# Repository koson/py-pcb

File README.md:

# py-pcb
pcb dei sistemi py-acqua e py-home

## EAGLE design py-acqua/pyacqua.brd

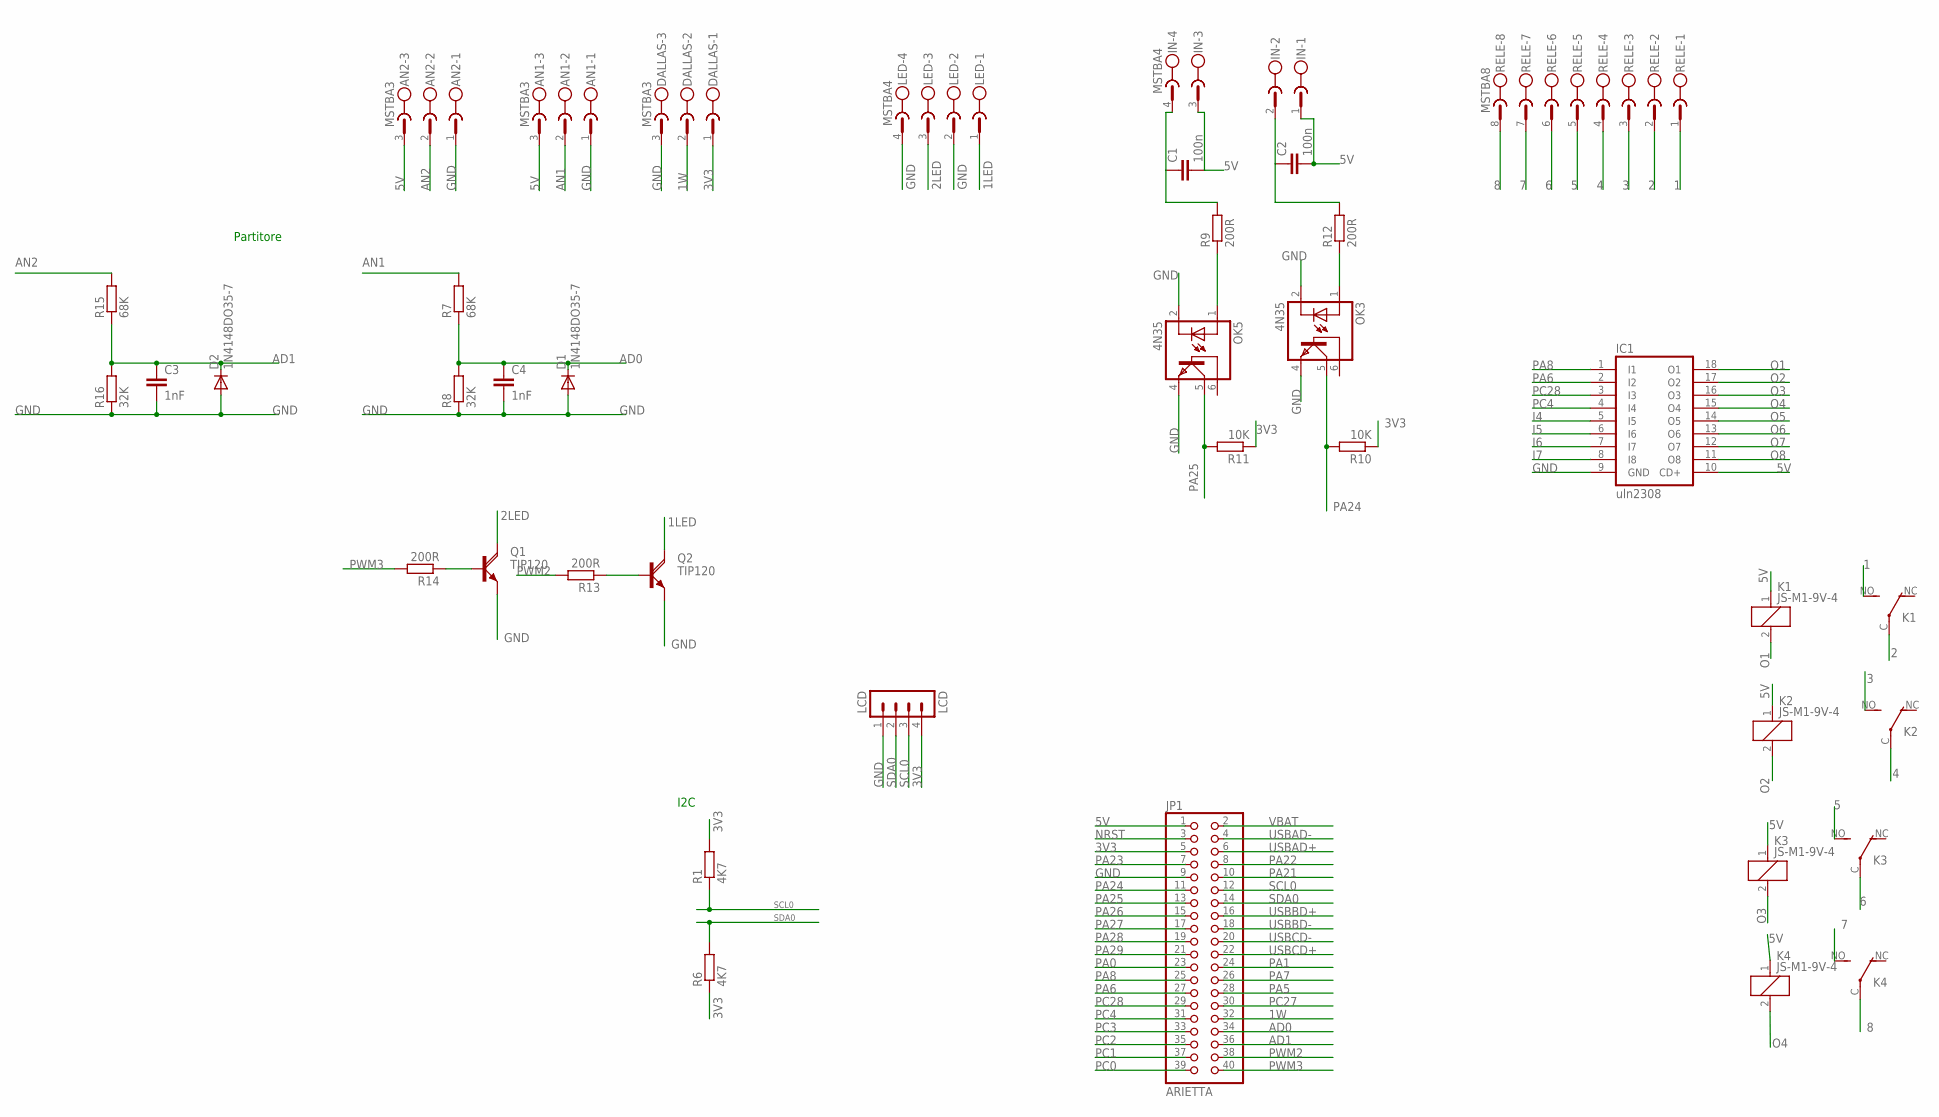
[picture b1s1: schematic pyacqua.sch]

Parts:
AN1, AN2: MSTBA3
C1, C2: 100n; C2.5-3
C3, C4: 1nF; C2.5-3
D1, D2: 1N4148DO35-7; DO35-7
DALLAS: MSTBA3
IC1: uln2308; DIL18
IN: MSTBA4
JP1: ARIETTA; 2X20
K1, K2, K3, K4: JS-M1-9V-4; JS-M
LCD: LCD; MA04-1
LED: MSTBA4
OK3, OK5: 4N35; DIL06
Q1, Q2: TIP120; TO220AH
R1, R6: 4K7; 0204V
R7, R15: 68K; 0204V
R8, R16: 32K; 0204V
R9, R12, R13, R14: 200R; 0204V
R10, R11: 10K; 0204V
RELE: MSTBA8

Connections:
1: K1.NO (S), RELE.1
1LED: LED.1, Q2.C
1W: DALLAS.2, JP1.32
2: K1.C, RELE.2
2LED: LED.3, Q1.C
3: K2.NO (S), RELE.3
3V3: DALLAS.1, JP1.5, LCD.4, R1.2, R6.1, R10.1, R11.1
4: K2.C, RELE.4
5: K3.NO (S), RELE.5
5V: AN1.3, AN2.3, C1.2, C2.2, IC1.10 (CD+), IN.1, IN.3, JP1.1, K1.1, K2.1, K3.1, K4.1
6: K3.C, RELE.6
7: K4.NO (S), RELE.7
8: K4.C, RELE.8
AD0: C4.1, D1.C, JP1.34, R7.1, R8.2
AD1: C3.1, D2.C, JP1.36, R15.1, R16.2
AN1: AN1.2, R7.2
AN2: AN2.2, R15.2
GND: AN1.1, AN2.1, C3.2, C4.2, D1.A, D2.A, DALLAS.3, IC1.9 (GND), JP1.9, LCD.1, LED.2, LED.4, OK3.2 (C), OK3.4 (EMI), OK5.2 (C), OK5.4 (EMI), Q1.E, Q2.E, R8.1, R16.1
I4: IC1.5 (I5)
I5: IC1.6 (I6)
I6: IC1.7 (I7)
I7: IC1.8 (I8)
unnamed: OK5.1 (A), R9.1
unnamed: OK3.1 (A), R12.1
unnamed: C2.1, IN.2, R12.2
unnamed: Q2.B, R13.1
unnamed: C1.1, IN.4, R9.2
unnamed: Q1.B, R14.1
NRST: JP1.3
O1: IC1.18 (O1), K1.2
O2: IC1.17 (O2), K2.2
O3: IC1.16 (O3), K3.2
O4: IC1.15 (O4), K4.2
O5: IC1.14 (O5)
O6: IC1.13 (O6)
O7: IC1.12 (O7)
O8: IC1.11 (O8)
PA0: JP1.23
PA1: JP1.24
PA5: JP1.28
PA6: IC1.2 (I2), JP1.27
PA7: JP1.26
PA8: IC1.1 (I1), JP1.25
PA21: JP1.10
PA22: JP1.8
PA23: JP1.7
PA24: JP1.11, OK3.5 (COL), R10.2
PA25: JP1.13, OK5.5 (COL), R11.2
PA26: JP1.15
PA27: JP1.17
PA28: JP1.19
PA29: JP1.21
PC0: JP1.39
PC1: JP1.37
PC2: JP1.35
PC3: JP1.33
PC4: IC1.4 (I4), JP1.31
PC27: JP1.30
PC28: IC1.3 (I3), JP1.29
PWM2: JP1.38, R13.2
PWM3: JP1.40, R14.2
SCL0: JP1.12, LCD.3, R1.1
SDA0: JP1.14, LCD.2, R6.2
USBAD+: JP1.6
USBAD-: JP1.4
USBBD+: JP1.16
USBBD-: JP1.18
USBCD+: JP1.22
USBCD-: JP1.20
VBAT: JP1.2

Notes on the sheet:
Partitore
I2C

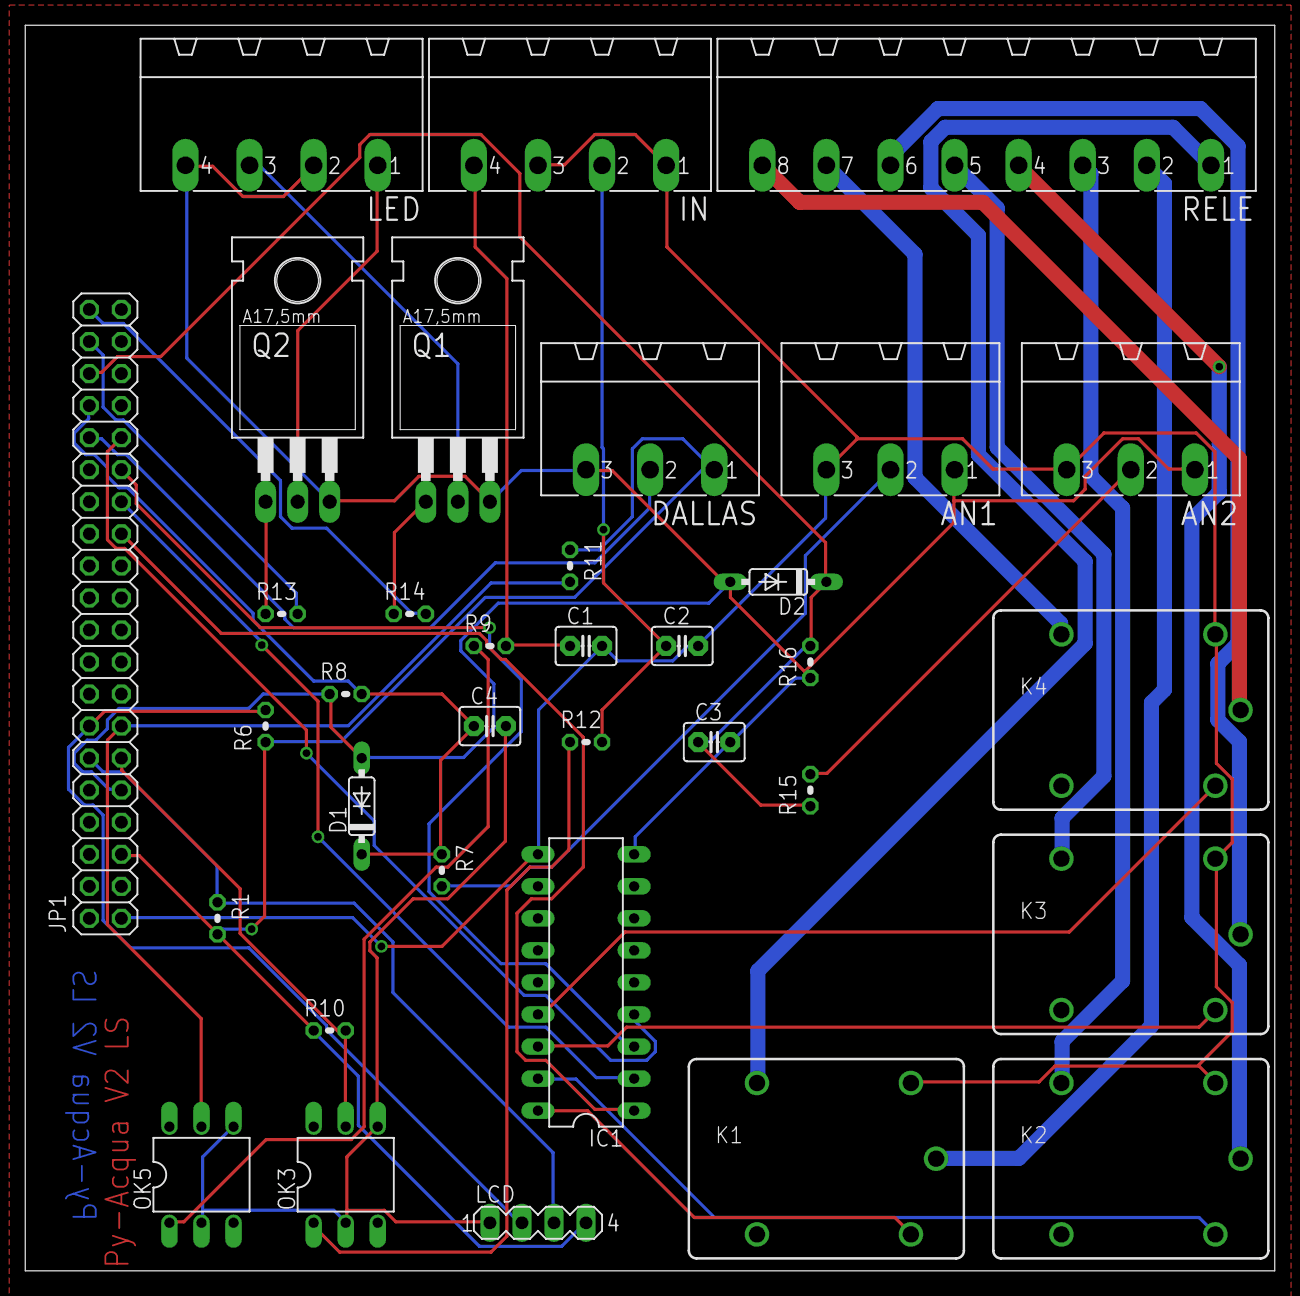
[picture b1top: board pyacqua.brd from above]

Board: 2 copper layers, 99.0 x 98.7 mm, 35 parts (0 on the bottom side), 38 nets.

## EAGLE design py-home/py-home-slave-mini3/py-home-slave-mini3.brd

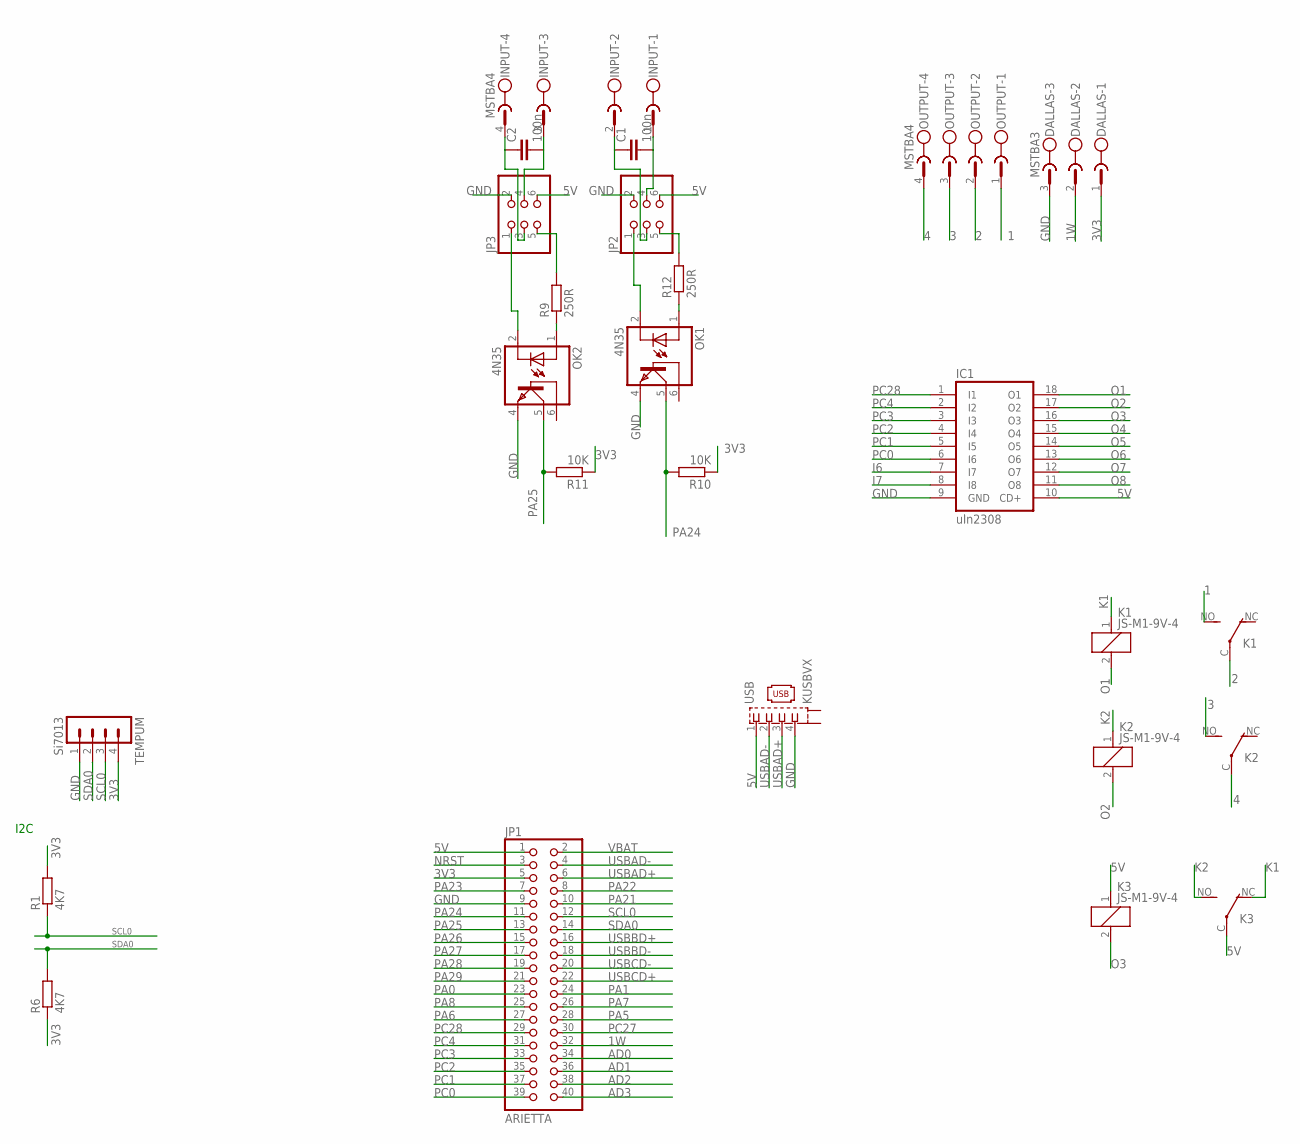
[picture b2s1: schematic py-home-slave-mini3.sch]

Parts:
C1, C2: 100n; C2.5-3
DALLAS: MSTBA3
IC1: uln2308; DIL18
INPUT: MSTBA4
JP1: ARIETTA; 2X20
JP2, JP3: PINHD-2X3; 2X03
K1, K2, K3: JS-M1-9V-4; JS-M
OK1, OK2: 4N35; DIL06
OUTPUT: MSTBA4
R1, R6: 4K7; 0204V
R9, R12: 250R; 0204V
R10, R11: 10K; 0204V
TEMPUM: Si7013; MA04-1
USB: KUSBVX

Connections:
1: K1.NO (S), OUTPUT.1
1W: DALLAS.2, JP1.32
2: K1.C, OUTPUT.2
3: K2.NO (S), OUTPUT.3
3V3: DALLAS.1, JP1.5, R1.2, R6.1, R10.1, R11.1, TEMPUM.4
4: K2.C, OUTPUT.4
5V: IC1.10 (CD+), JP1.1, JP2.6, JP3.6, K3.1, K3.C, USB.1
AD0: JP1.34
AD1: JP1.36
AD2: JP1.38
AD3: JP1.40
GND: DALLAS.3, IC1.9 (GND), JP1.9, JP2.2, JP3.2, OK1.4 (EMI), OK2.4 (EMI), TEMPUM.1, USB.4
I6: IC1.7 (I7)
I7: IC1.8 (I8)
K1: K1.1, K3.NC (O)
K2: K2.1, K3.NO (S)
unnamed: OK2.1 (A), R9.1
unnamed: C1.2, INPUT.1, JP2.4
unnamed: OK1.1 (A), R12.1
unnamed: JP2.1, OK1.2 (C)
unnamed: JP3.5, R9.2
unnamed: JP3.1, OK2.2 (C)
unnamed: JP2.5, R12.2
unnamed: C2.2, INPUT.3, JP3.4
unnamed: C1.1, INPUT.2, JP2.3
unnamed: C2.1, INPUT.4, JP3.3
NRST: JP1.3
O1: IC1.18 (O1), K1.2
O2: IC1.17 (O2), K2.2
O3: IC1.16 (O3), K3.2
O4: IC1.15 (O4)
O5: IC1.14 (O5)
O6: IC1.13 (O6)
O7: IC1.12 (O7)
O8: IC1.11 (O8)
PA0: JP1.23
PA1: JP1.24
PA5: JP1.28
PA6: JP1.27
PA7: JP1.26
PA8: JP1.25
PA21: JP1.10
PA22: JP1.8
PA23: JP1.7
PA24: JP1.11, OK1.5 (COL), R10.2
PA25: JP1.13, OK2.5 (COL), R11.2
PA26: JP1.15
PA27: JP1.17
PA28: JP1.19
PA29: JP1.21
PC0: IC1.6 (I6), JP1.39
PC1: IC1.5 (I5), JP1.37
PC2: IC1.4 (I4), JP1.35
PC3: IC1.3 (I3), JP1.33
PC4: IC1.2 (I2), JP1.31
PC27: JP1.30
PC28: IC1.1 (I1), JP1.29
SCL0: JP1.12, R1.1, TEMPUM.3
SDA0: JP1.14, R6.2, TEMPUM.2
USBAD+: JP1.6, USB.3
USBAD-: JP1.4, USB.2
USBBD+: JP1.16
USBBD-: JP1.18
USBCD+: JP1.22
USBCD-: JP1.20
VBAT: JP1.2

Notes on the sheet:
I2C

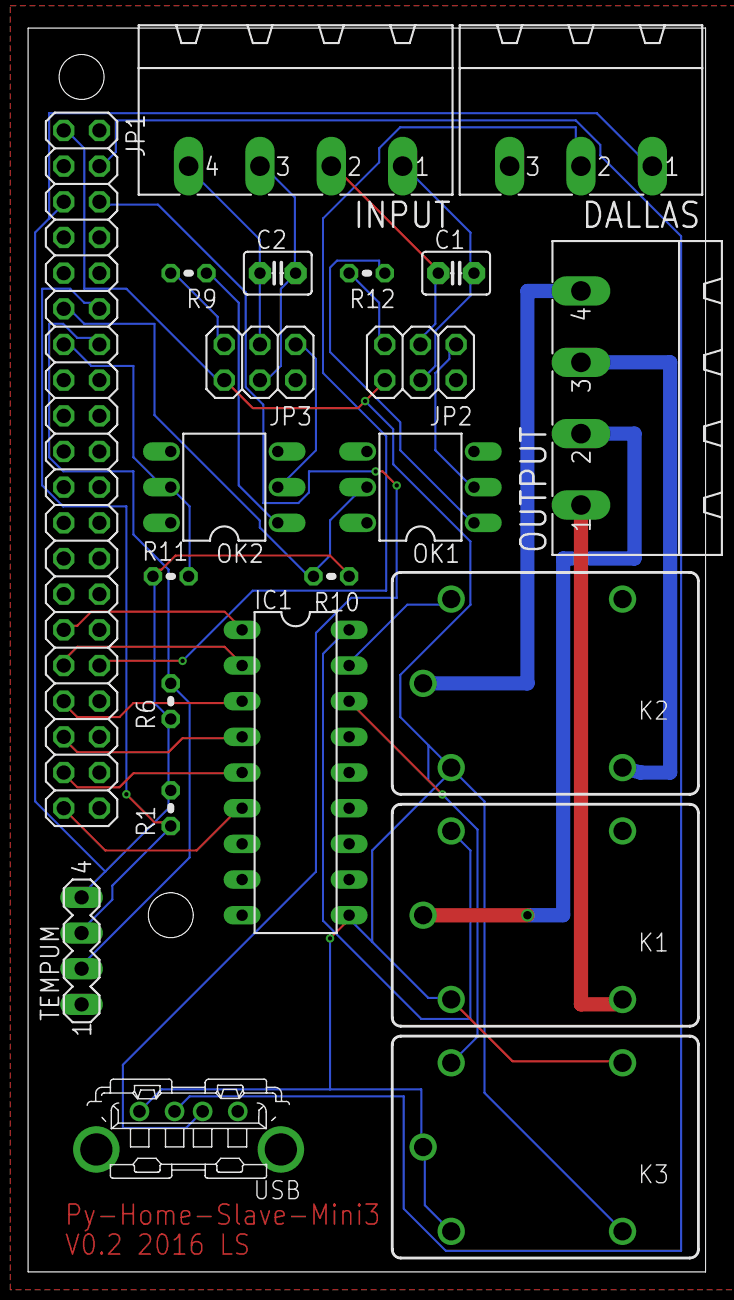
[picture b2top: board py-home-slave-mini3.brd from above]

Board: 2 copper layers, 48.2 x 88.6 mm, 22 parts (0 on the bottom side), 35 nets.

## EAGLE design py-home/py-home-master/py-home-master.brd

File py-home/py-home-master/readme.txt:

I2C
PA30 (SDA0) and PA31 (SCL0) towards 3.3V.

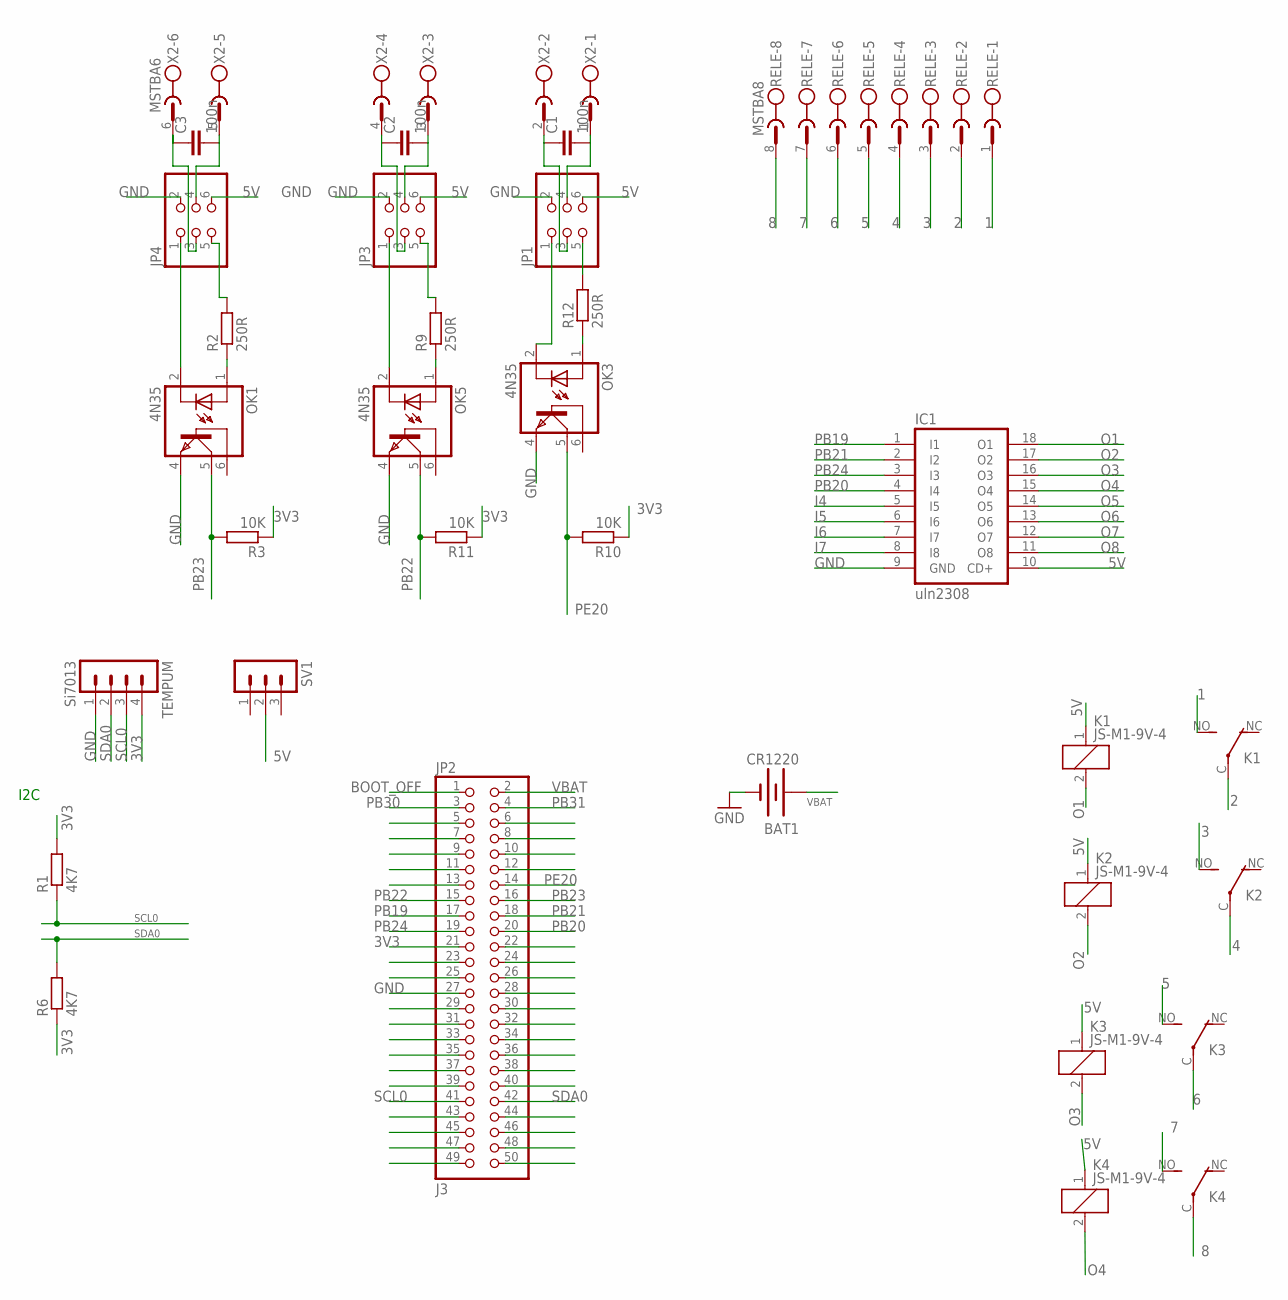
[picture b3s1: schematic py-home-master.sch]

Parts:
BAT1: CR1220; BAT_CR1220
C1, C2, C3: 100n; C2.5-3
IC1: uln2308; DIL18
JP1, JP3, JP4: PINHD-2X3; 2X03
JP2: J3; 2X25
K1, K2, K3, K4: JS-M1-9V-4; JS-M
OK1, OK3, OK5: 4N35; DIL06
R1, R6: 4K7; 0204V
R2, R9, R12: 250R; 0204V
R3, R10, R11: 10K; 0204V
RELE: MSTBA8
SV1: MA03-1
TEMPUM: Si7013; MA04-1
X2: MSTBA6

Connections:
1: K1.NO (S), RELE.1
2: K1.C, RELE.2
3: K2.NO (S), RELE.3
3V3: JP2.21, R1.2, R3.1, R6.1, R10.1, R11.1, TEMPUM.4
4: K2.C, RELE.4
5: K3.NO (S), RELE.5
5V: IC1.10 (CD+), JP1.6, JP3.6, JP4.6, K1.1, K2.1, K3.1, K4.1, SV1.2
6: K3.C, RELE.6
7: K4.NO (S), RELE.7
8: K4.C, RELE.8
BOOT_OFF: JP2.1
GND: BAT1.GND (-), IC1.9 (GND), JP1.2, JP2.27, JP3.2, JP4.2, OK1.4 (EMI), OK3.4 (EMI), OK5.4 (EMI), TEMPUM.1
I4: IC1.5 (I5)
I5: IC1.6 (I6)
I6: IC1.7 (I7)
I7: IC1.8 (I8)
unnamed: OK5.1 (A), R9.1
unnamed: JP1.5, R12.2
unnamed: OK3.1 (A), R12.1
unnamed: JP1.1, OK3.2 (C)
unnamed: OK1.1 (A), R2.1
unnamed: JP4.1, OK1.2 (C)
unnamed: C2.1, JP3.3, X2.4
unnamed: C3.1, JP4.3, X2.6
unnamed: C1.1, JP1.3, X2.2
unnamed: JP3.1, OK5.2 (C)
unnamed: C1.2, JP1.4, X2.1
unnamed: C2.2, JP3.4, X2.3
unnamed: JP3.5, R9.2
unnamed: C3.2, JP4.4, X2.5
unnamed: JP4.5, R2.2
O1: IC1.18 (O1), K1.2
O2: IC1.17 (O2), K2.2
O3: IC1.16 (O3), K3.2
O4: IC1.15 (O4), K4.2
O5: IC1.14 (O5)
O6: IC1.13 (O6)
O7: IC1.12 (O7)
O8: IC1.11 (O8)
PB19: IC1.1 (I1), JP2.17
PB20: IC1.4 (I4), JP2.20
PB21: IC1.2 (I2), JP2.18
PB22: JP2.15, OK5.5 (COL), R11.2
PB23: JP2.16, OK1.5 (COL), R3.2
PB24: IC1.3 (I3), JP2.19
PB30: JP2.3
PB31: JP2.4
PE20: JP2.14, OK3.5 (COL), R10.2
SCL0: JP2.41, R1.1, TEMPUM.3
SDA0: JP2.42, R6.2, TEMPUM.2
VBAT: BAT1.V+ (+), JP2.2

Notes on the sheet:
I2C

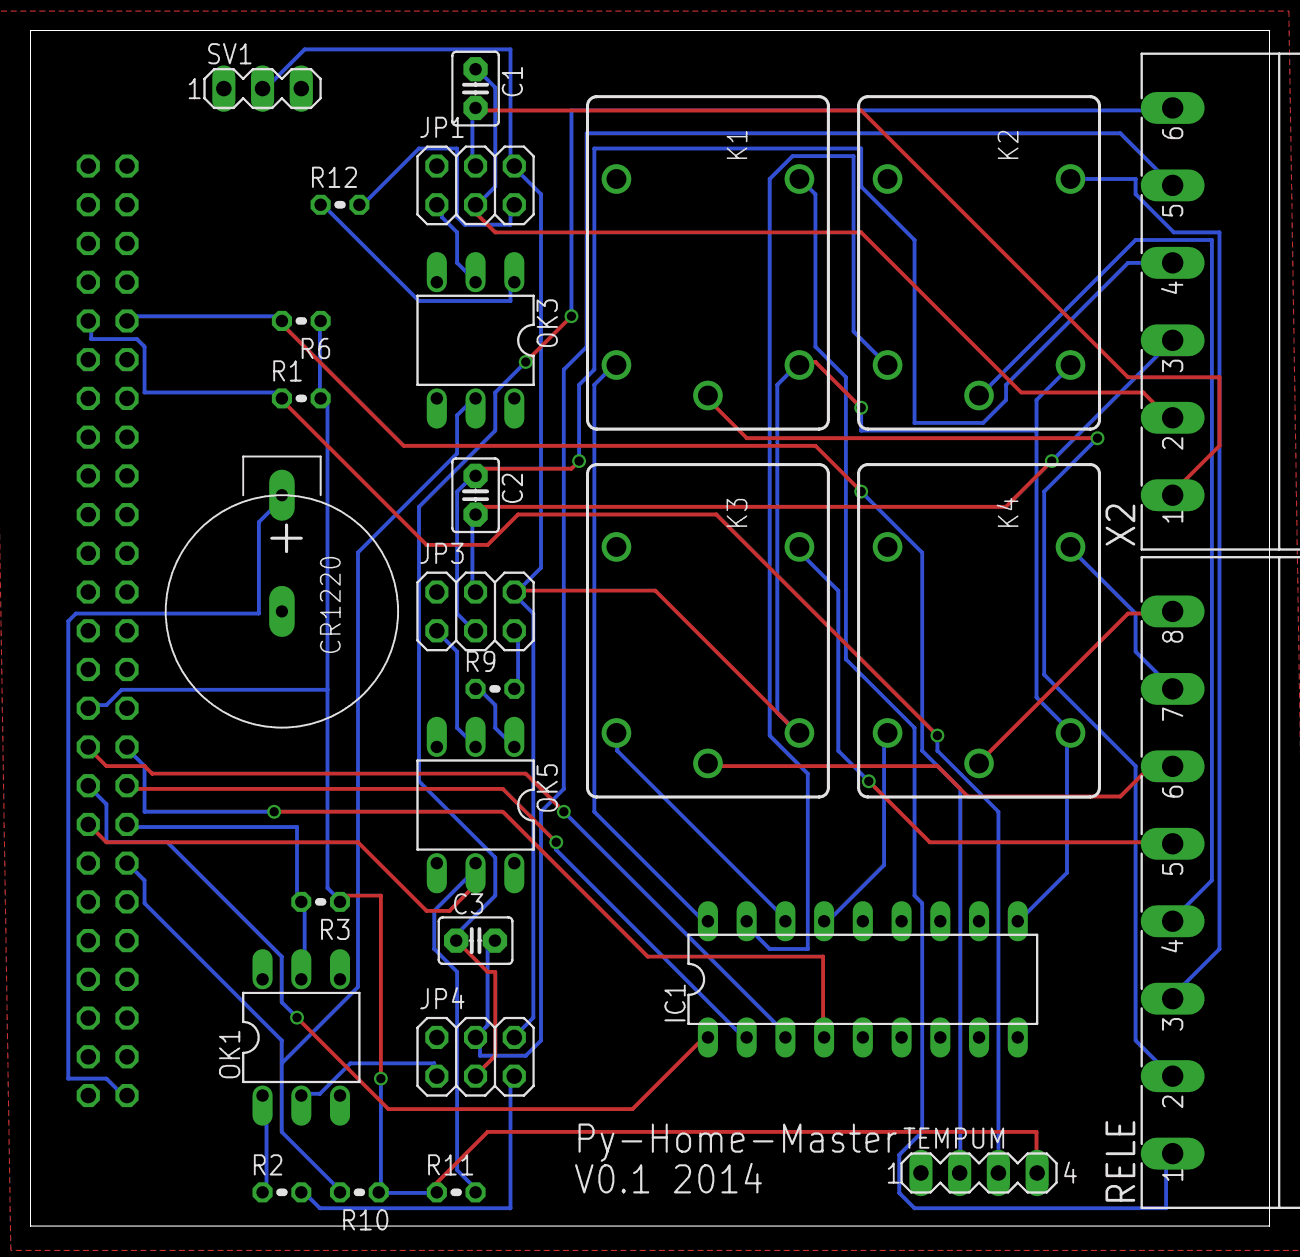
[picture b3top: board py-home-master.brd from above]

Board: 2 copper layers, 81.3 x 78.4 mm, 28 parts (1 on the bottom side), 40 nets.
